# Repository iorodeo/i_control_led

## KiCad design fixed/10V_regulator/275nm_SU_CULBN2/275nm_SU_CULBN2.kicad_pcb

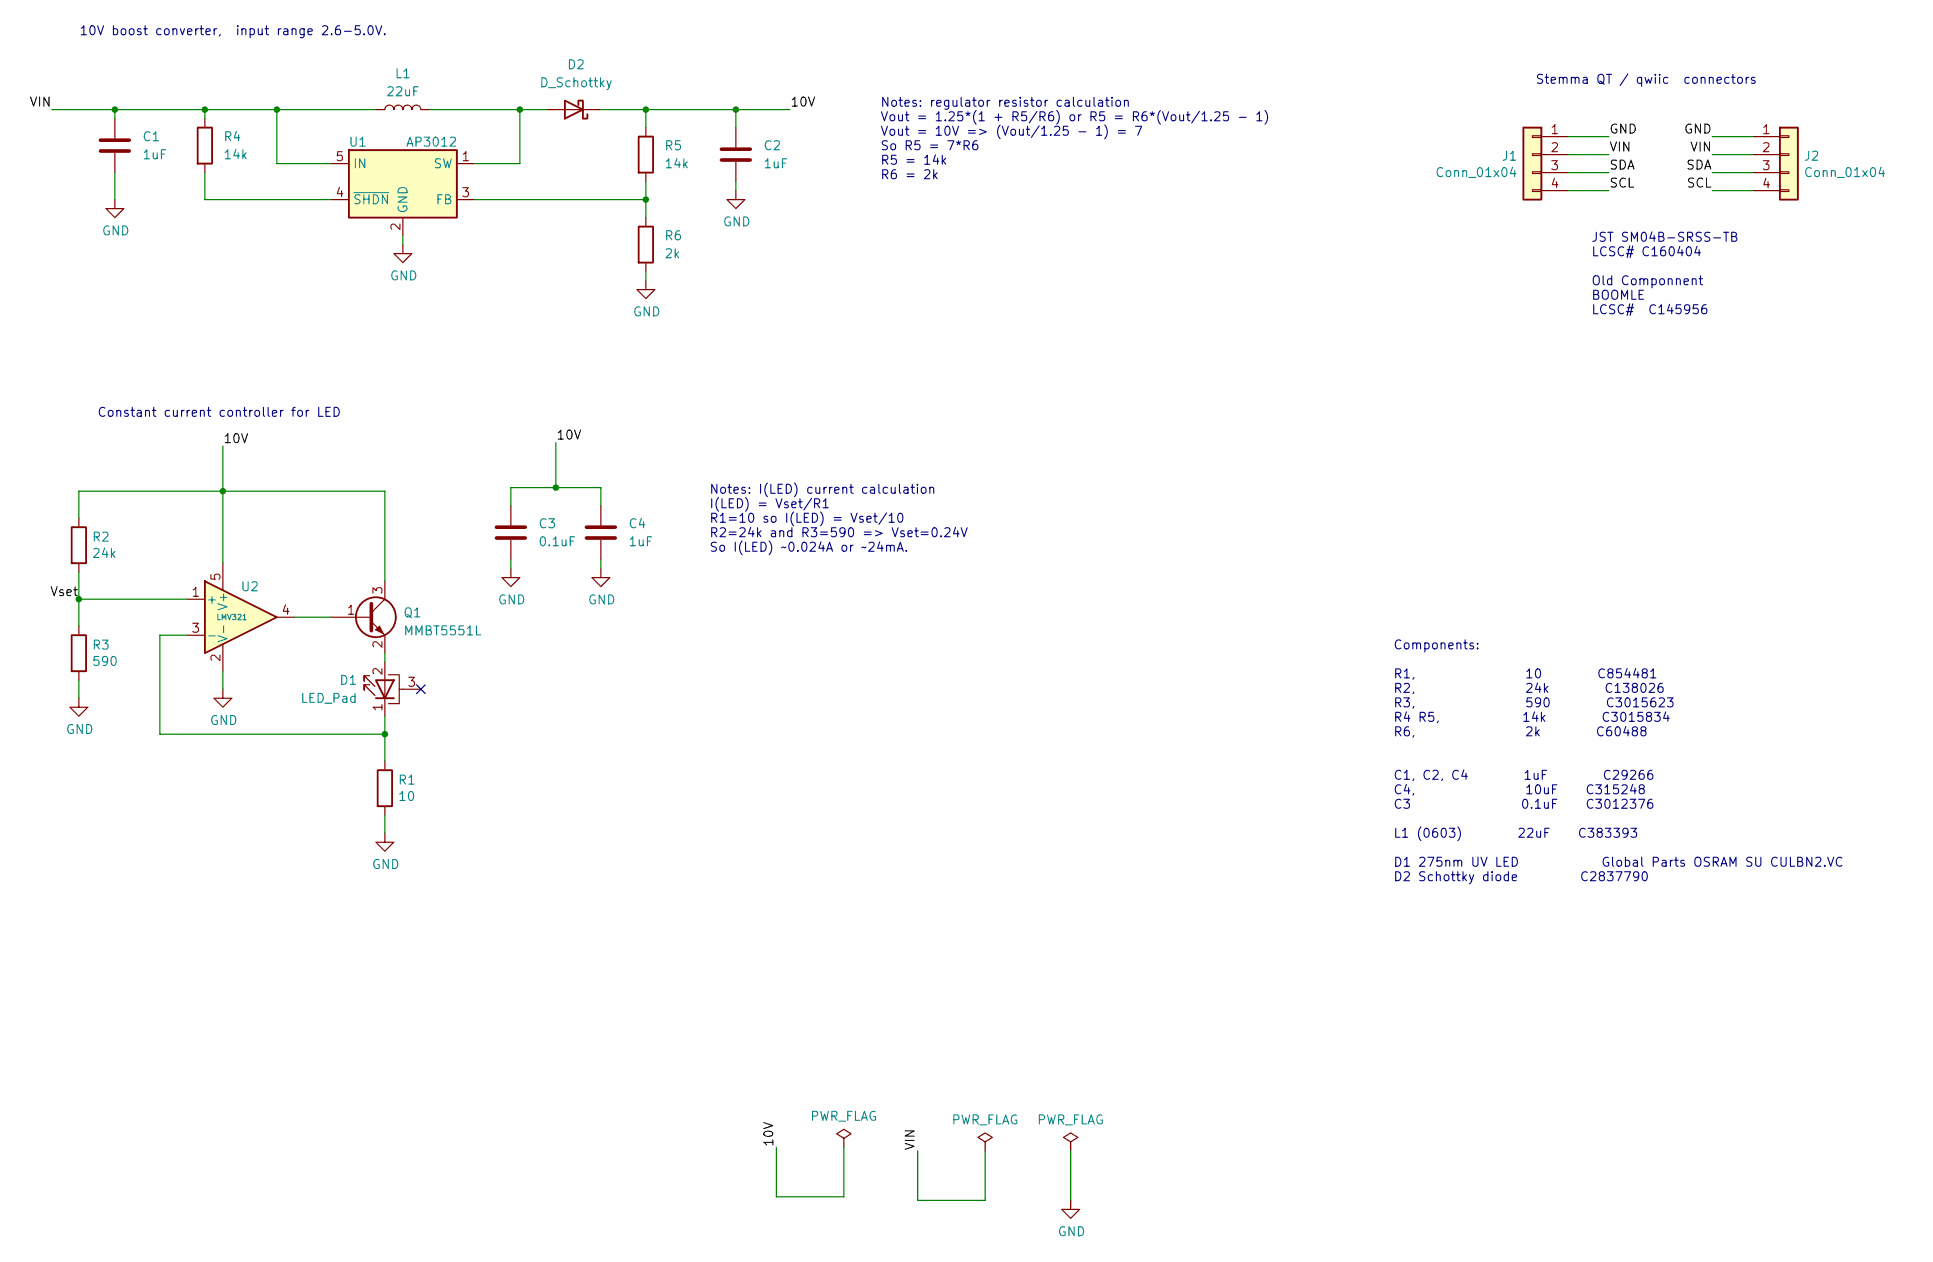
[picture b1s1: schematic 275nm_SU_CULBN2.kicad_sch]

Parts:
C1, C2, C4: 1uF; C_0402_1005Metric
C3: 0.1uF; C_0402_1005Metric
D1: LED_Pad; LED_1414
D2: D_Schottky; D_0402_1005Metric
J1, J2: Conn_01x04; JST_SH_SM04B-SRSS-TB_1x04-1MP_P1.00mm_Horizontal
L1: 22uF; L_0603_1608Metric
Q1: MMBT5551L; SOT-23
R1: 10; R_0402_1005Metric
R2: 24k; R_0402_1005Metric
R3: 590; R_0402_1005Metric
R4, R5: 14k; R_0402_1005Metric
R6: 2k; R_0402_1005Metric
U1: AP3012; SOT-23-5
U2: LMV321; SOT-23-5

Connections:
/10V: C2.2, C3.1, C4.1, D2.1 (K), Q1.3 (C), R2.1, R5.1, U2.5 (V+)
/SCL: J1.4, J2.4
/SDA: J1.3, J2.3
/VIN: C1.2, J1.2, J2.2, L1.1, R4.1, U1.5 (IN)
/Vset: R2.2, R3.1, U2.1 (+)
GND: C1.1, C2.1, C3.2, C4.2, J1.1, J2.1, R1.2, R3.2, R6.2, U1.2 (GND), U2.2 (V-)
unnamed: D1.2 (A), Q1.2 (E)
unnamed: D1.1 (K), R1.1, U2.3 (-)
unnamed: D2.2 (A), L1.2, U1.1 (SW)
unnamed: Q1.1 (B), U2.4
unnamed: R5.2, R6.1, U1.3 (FB)
unnamed: R4.2, U1.4 (~SHDN)

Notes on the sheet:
JST SM04B-SRSS-TB LCSC# C160404 Old Componnent BOOMLE LCSC# C145956
Stemma QT / qwiic connectors
Components: R1, 10 C854481 R2, 24k C138026 R3, 590 C3015623 R4 R5, 14k C3015834 R6, 2k C60488 C1, C2, C4 1uF C29266 C4, 10uF C315248 C3 0.1uF C3012376 L1 (0603) 22uF C383393 D1 275nm UV LED Global Parts OSRAM SU CULBN2.VC D2 Schottky diode C2837790
Constant current controller for LED
10V boost converter, input range 2.6-5.0V.
Notes: regulator resistor calculation Vout = 1.25*(1 + R5/R6) or R5 = R6*(Vout/1.25 - 1) Vout = 10V => (Vout/1.25 - 1) = 7 So R5 = 7*R6 R5 = 14k R6 = 2k
Notes: I(LED) current calculation I(LED) = Vset/R1 R1=10 so I(LED) = Vset/10 R2=24k and R3=590 => Vset=0.24V So I(LED) ~0.024A or ~24mA.

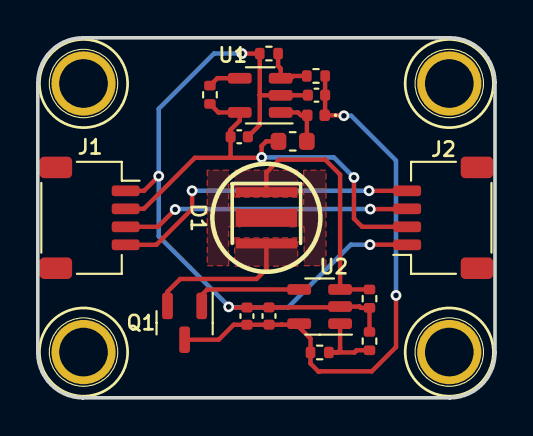
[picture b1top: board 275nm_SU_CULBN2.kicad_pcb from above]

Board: 2 copper layers, 25.4 x 20.0 mm, 22 parts (0 on the bottom side), 12 nets.

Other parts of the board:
M1, M2, M3, M4: MountingHole_2.5mm_Pad

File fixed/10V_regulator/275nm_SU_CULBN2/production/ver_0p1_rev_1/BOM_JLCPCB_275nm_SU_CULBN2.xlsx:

Comment | Designator | Footprint | LCSC Part #（optional） | Qty
1uF Ceramic Capacitor | C1,C2,C4 | 0402 | C29266 | 3
0.1uF Ceramic Capacitor | C3 | 0402 | C3012376 | 1
275nm UV LED | D1 | 1414 | C5762581 | 1
Schottky Barrier Diode | D2 | 0402 | C2837790 | 1
4-Pin Connector, JST SM04B-SRSS-TB | J1 ,J2 | SMD,P=1mm | C160404 | 2
22uH Inductor | L1 | 0603 | C383393 | 1
MMBT5551LT1G Bipolar Transistor, 600mA NPN | Q1 | SOT-23 | C41095 | 1
10Ω ±1% Resistor | R1 | 0402 | C854481 | 1
24kΩ ±1% Resistor | R2 | 0402 | C138026 | 1
590Ω ±1% Resistor | R3 | 0402 | C3015623 | 1
14kΩ ±1% Resistor | R4,R5 | 0402 | C3015834 | 2
2kΩ ±1% Resistor | R6 | 0402 | C60488 | 1
AP3012KTR-E1 boost converter | U1 | SOT-23-5 | C460356 | 1
LMV321 Operational Amplifier | U2 | SOT-23-5 | C686637 | 1
